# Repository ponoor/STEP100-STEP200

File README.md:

# STEP100-STEP200
Some accessories for STEP100 and STEP200

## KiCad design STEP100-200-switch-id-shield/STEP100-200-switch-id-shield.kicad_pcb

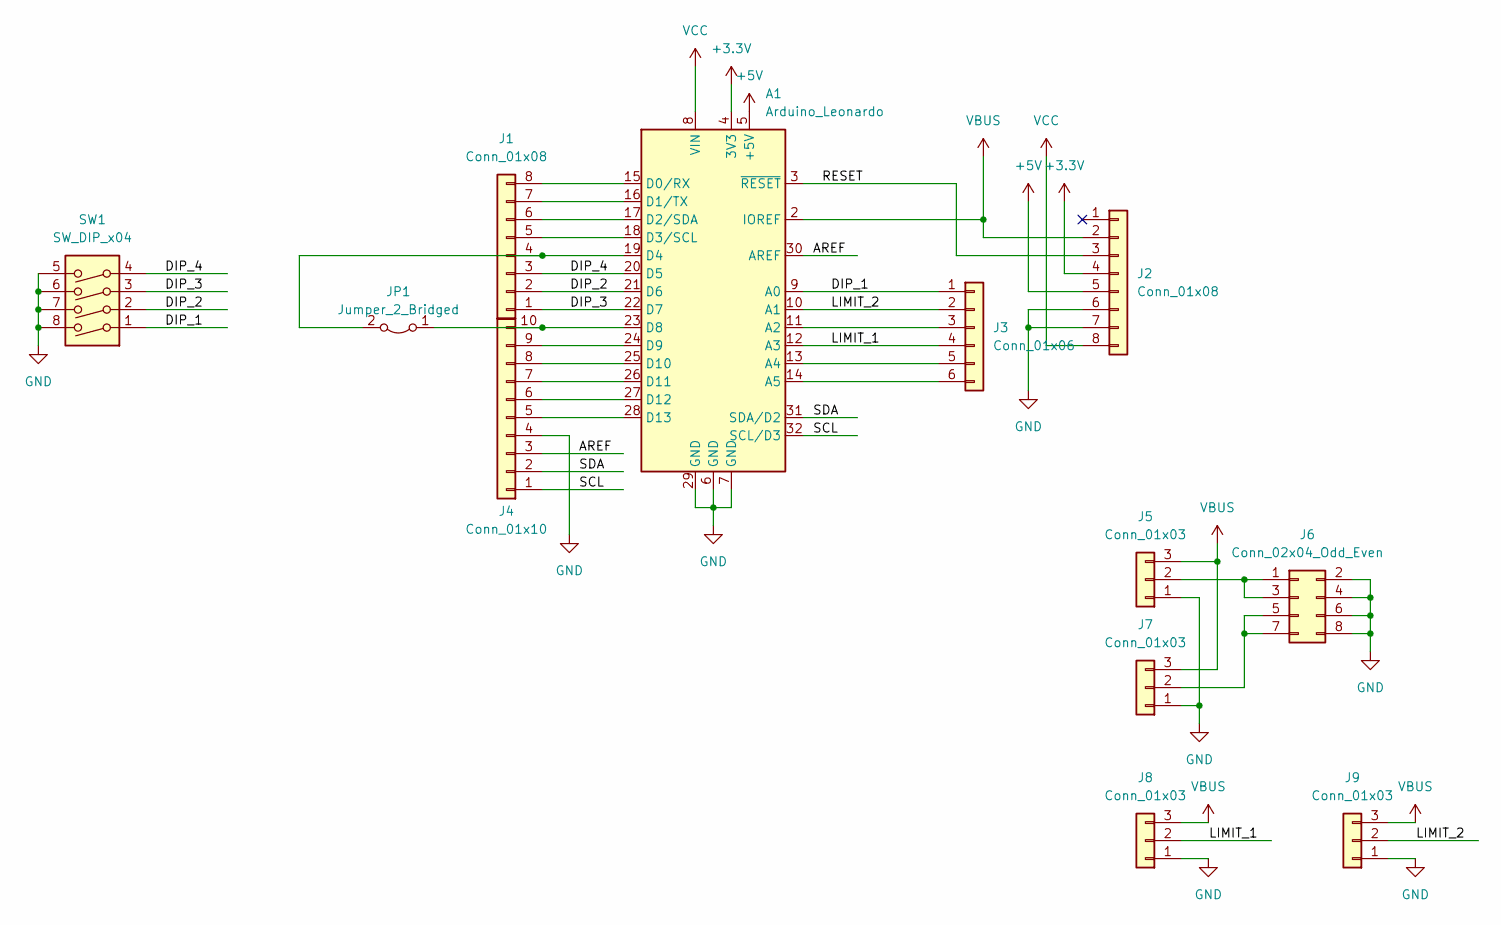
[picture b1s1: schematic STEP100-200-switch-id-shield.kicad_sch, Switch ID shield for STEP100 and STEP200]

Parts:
A1: Arduino_Leonardo; Arduino_UNO_R3
J1, J2: Conn_01x08; PinSocket_1x08_P2.54mm_Vertical
J3: Conn_01x06; PinSocket_1x06_P2.54mm_Vertical
J4: Conn_01x10; PinSocket_1x10_P2.54mm_Vertical
J5, J7, J8, J9: Conn_01x03; JST_XA_B03B-XASK-1_1x03_P2.50mm_Vertical
J6: Conn_02x04_Odd_Even; PinSocket_2x04_P2.54mm_Vertical
JP1: Jumper_2_Bridged; SolderJumper-2_P1.3mm_Bridged_Pad1.0x1.5mm
SW1: SW_DIP_x04; SW_DIP_SPSTx04_Slide_9.78x12.34mm_W7.62mm_P2.54mm

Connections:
+3.3V: A1.4 (3V3), J2.4
+5V: A1.5 (+5V), J2.5
/AREF: A1.30 (AREF), J4.3
/DIP_1: A1.9 (A0), J3.1, SW1.1
/DIP_2: A1.21 (D6), J1.2, SW1.2
/DIP_3: A1.22 (D7), J1.1, SW1.3
/DIP_4: A1.20 (D5), J1.3, SW1.4
/LIMIT_1: A1.12 (A3), J3.4, J8.2
/LIMIT_2: A1.10 (A1), J3.2, J9.2
/RESET: A1.3 (~RESET), J2.3
/SCL: A1.32 (SCL/D3), J4.1
/SDA: A1.31 (SDA/D2), J4.2
GND: A1.6 (GND), A1.7 (GND), A1.29 (GND), J2.6, J2.7, J4.4, J5.1, J6.2, J6.4, J6.6, J6.8, J7.1, J8.1, J9.1, SW1.5, SW1.6, SW1.7, SW1.8
unnamed: A1.11 (A2), J3.3
unnamed: A1.13 (A4), J3.5
unnamed: A1.14 (A5), J3.6
unnamed: A1.15 (D0/RX), J1.8
unnamed: A1.16 (D1/TX), J1.7
unnamed: A1.17 (D2/SDA), J1.6
unnamed: A1.18 (D3/SCL), J1.5
unnamed: A1.19 (D4), J1.4, JP1.2 (B)
unnamed: A1.23 (D8), J4.10, JP1.1 (A)
unnamed: A1.24 (D9), J4.9
unnamed: A1.25 (D10), J4.8
unnamed: A1.26 (D11), J4.7
unnamed: A1.27 (D12), J4.6
unnamed: A1.28 (D13), J4.5
unnamed: J5.2, J6.1, J6.3
unnamed: J6.5, J6.7, J7.2
VBUS: A1.2 (IOREF), J2.2, J5.3, J7.3, J8.3, J9.3
VCC: A1.8 (VIN), J2.8

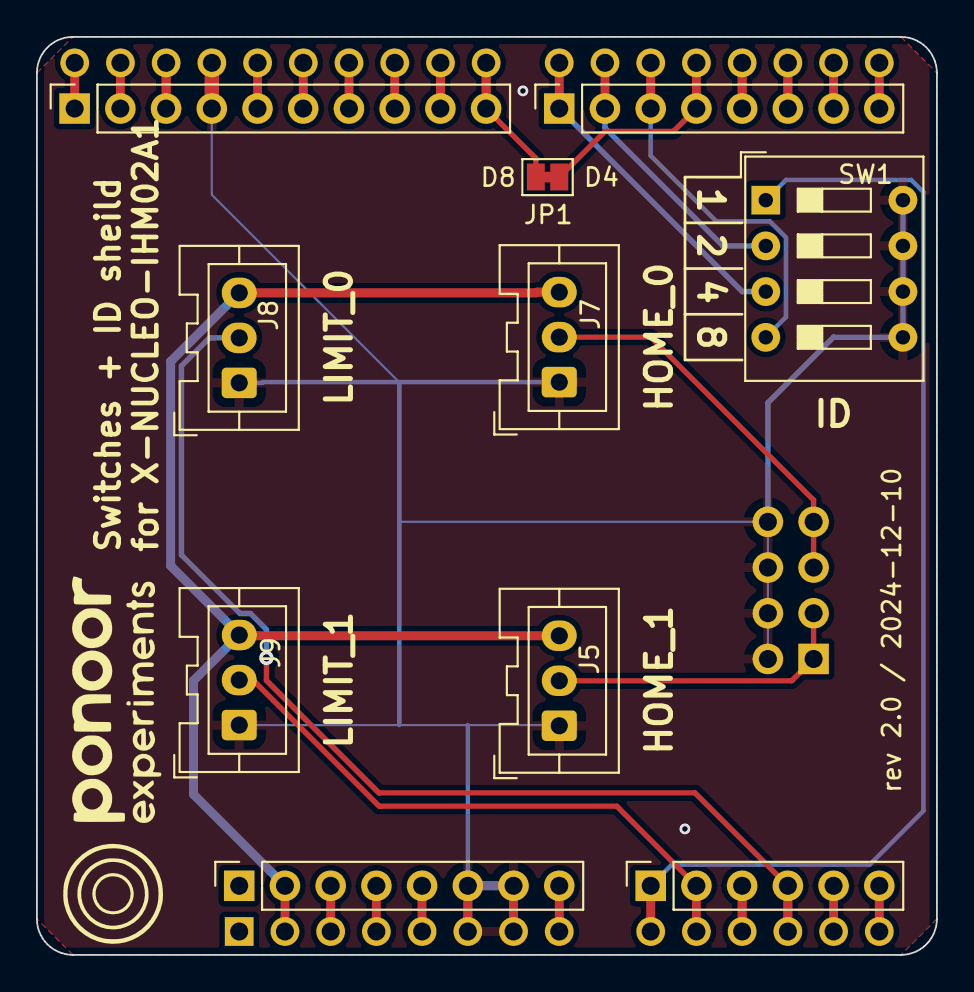
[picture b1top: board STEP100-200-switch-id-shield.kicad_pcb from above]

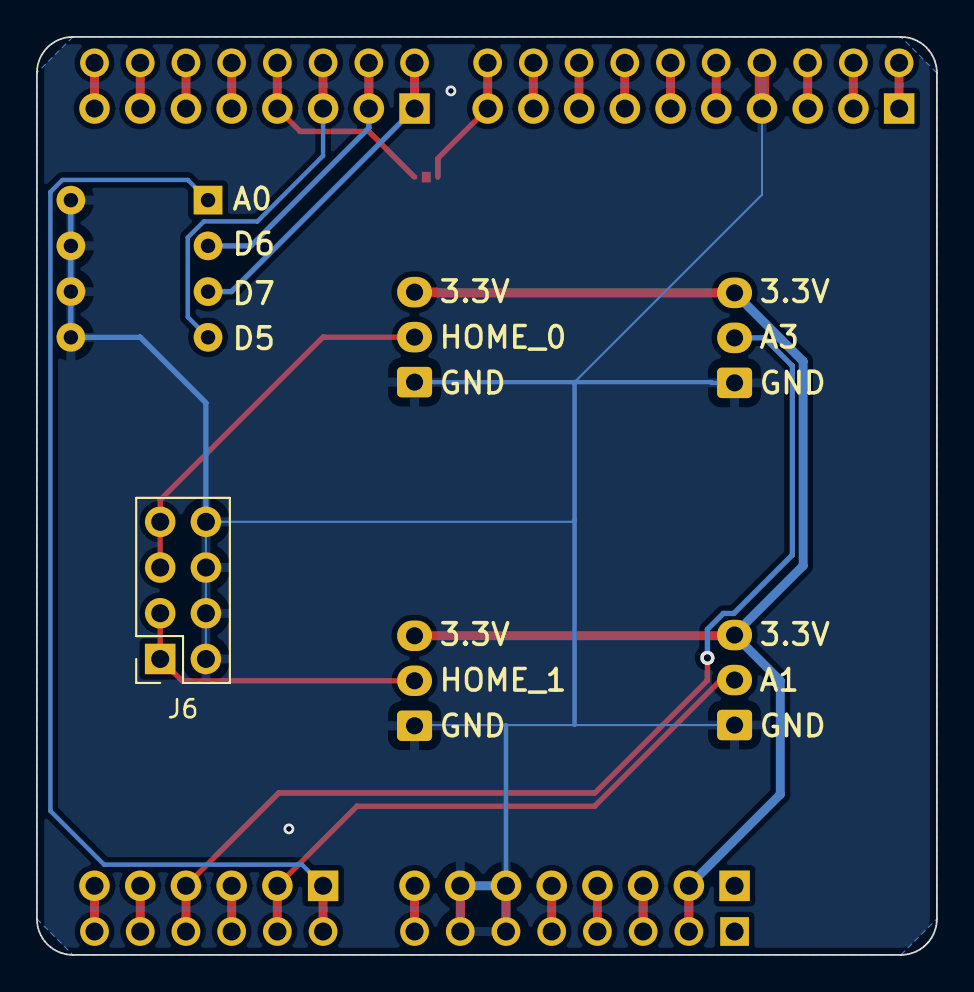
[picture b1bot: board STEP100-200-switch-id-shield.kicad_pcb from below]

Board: 2 copper layers, 50.0 x 51.0 mm, 12 parts (2 on the bottom side), 31 nets.

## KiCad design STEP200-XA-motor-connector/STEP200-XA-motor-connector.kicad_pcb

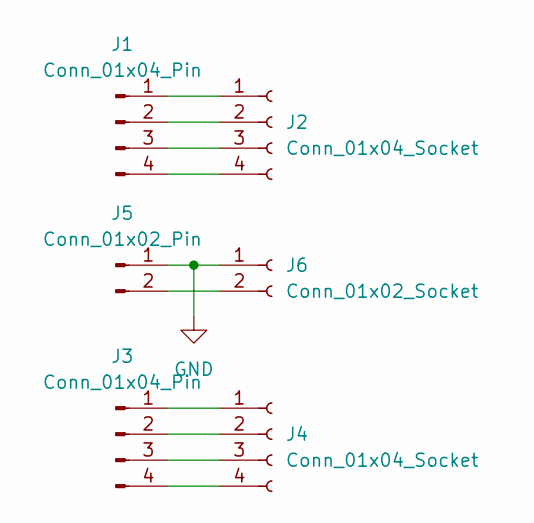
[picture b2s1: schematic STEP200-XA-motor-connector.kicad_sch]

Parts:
J1, J3: Conn_01x04_Pin; JST_VH_B4P-VH_1x04_P3.96mm_Vertical
J2, J4: Conn_01x04_Socket; JST_XA_B04B-XASK-1_1x04_P2.50mm_Vertical
J5: Conn_01x02_Pin; JST_VH_B2P-VH_1x02_P3.96mm_Vertical
J6: Conn_01x02_Socket; PhoenixContact_MCV_1,5_2-G-3.81_1x02_P3.81mm_Vertical

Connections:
GND: J5.1, J6.1
unnamed: J1.1, J2.1
unnamed: J1.2, J2.2
unnamed: J1.3, J2.3
unnamed: J1.4, J2.4
unnamed: J3.1, J4.1
unnamed: J3.2, J4.2
unnamed: J3.3, J4.3
unnamed: J3.4, J4.4
unnamed: J5.2, J6.2

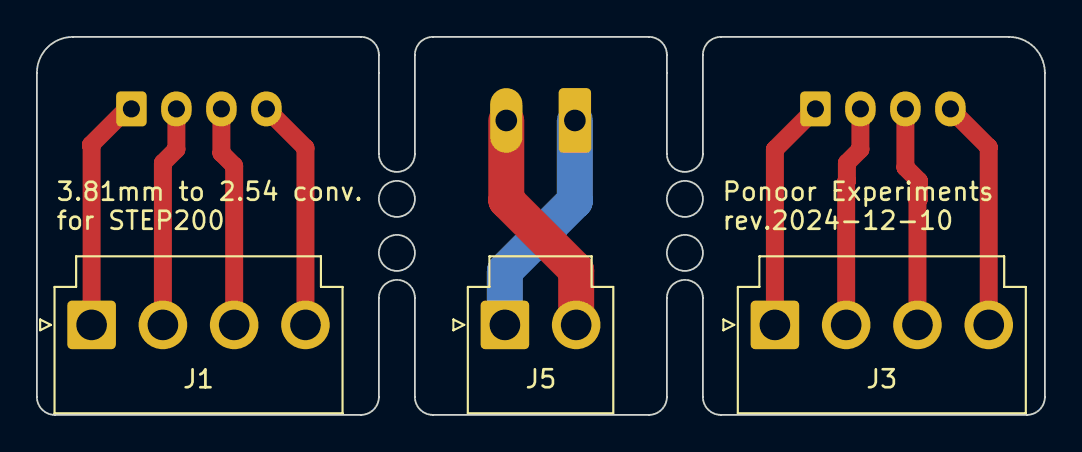
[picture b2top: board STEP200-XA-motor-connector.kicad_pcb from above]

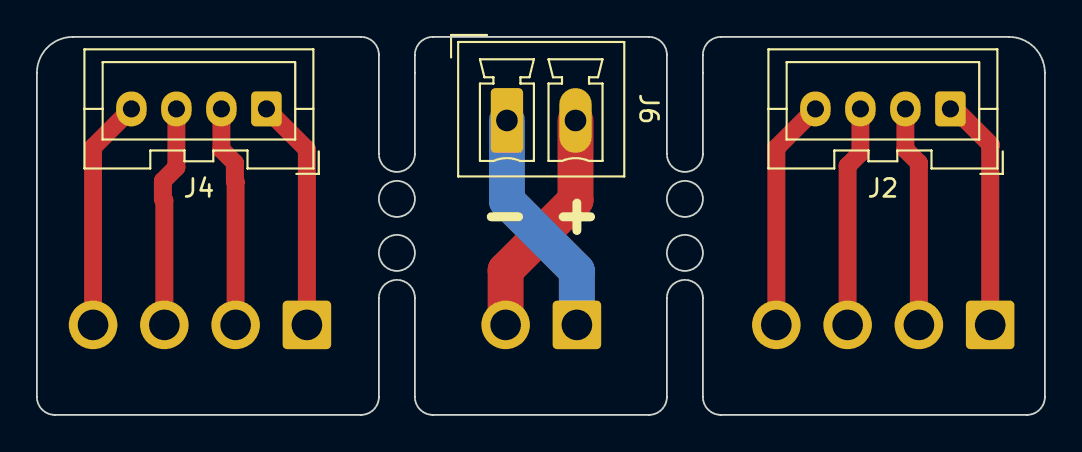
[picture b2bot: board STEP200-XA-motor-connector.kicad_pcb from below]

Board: 2 copper layers, 56.0 x 21.0 mm, 6 parts (3 on the bottom side), 10 nets.

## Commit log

2024-12-09 switch-id-shield initial commit
2024-12-10 STEP200 motor connector PCB initial commit
2024-12-10 update gitignore
2024-12-10 version 2 PCBs
